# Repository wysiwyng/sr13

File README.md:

sr13 - MAI
====

the team MAI student robotics 2013 award winning code - see here: 
- http://www.youtube.com/watch?v=O69H89OFcbA
- https://www.studentrobotics.org/
- https://www.studentrobotics.org/news/2013-04-14_jaws_meet_floors

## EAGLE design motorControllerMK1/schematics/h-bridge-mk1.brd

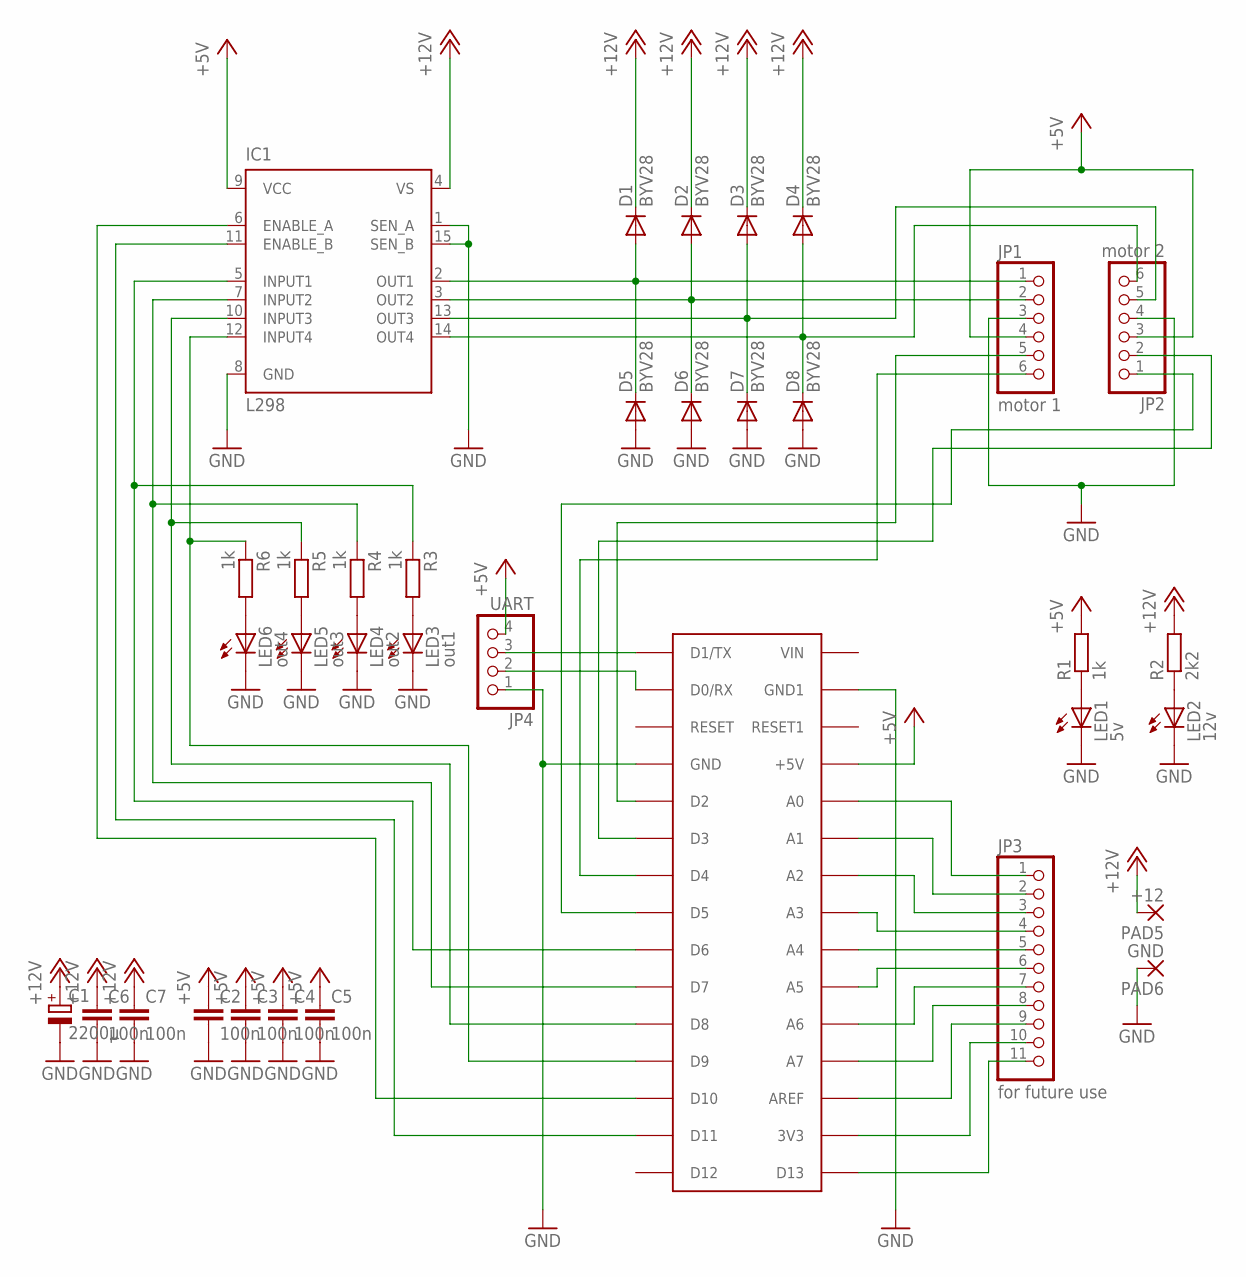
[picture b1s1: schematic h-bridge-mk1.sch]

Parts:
C1: 2200µ; E5-10,5
C2, C3, C4, C5, C6, C7: 100n; C025-025X050
D1, D2, D3, D4, D5, D6, D7, D8: BYV28; SOD64-10
IC1: L298; MULTIWATT-15
JP1: motor 1; 1X06
JP2: motor 2; 1X06
JP3: for future use; 1X11
JP4: UART; 1X04
LED1: 5v; LED3MM
LED2: 12v; LED3MM
LED3: out1; LED3MM
LED4: out2; LED3MM
LED5: out3; LED3MM
LED6: out4; LED3MM
PAD5: +12; 3,81/1,1
PAD6: GND; 3,81/1,1
R1, R3, R4, R5, R6: 1k; 0207/10
R2: 2k2; 0207/10
U$1: ARDUINONANO; PDIP-32

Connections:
+5V: C2.1, C3.1, C4.1, C5.1, IC1.9 (VCC), JP1.4, JP2.3, JP4.4, R1.2, U$1.+5V
+12V: C1.+, C6.1, C7.1, D1.C, D2.C, D3.C, D4.C, IC1.4 (VS), PAD5.1, R2.2
ENA: IC1.6 (ENABLE_A), U$1.D10
ENB: IC1.11 (ENABLE_B), U$1.D11
GND: C1.-, C2.2, C3.2, C4.2, C5.2, C6.2, C7.2, D5.A, D6.A, D7.A, D8.A, IC1.1 (SEN_A), IC1.8 (GND), IC1.15 (SEN_B), JP1.3, JP2.4, JP4.1, LED1.K (C), LED2.K (C), LED3.K (C), LED4.K (C), LED5.K (C), LED6.K (C), PAD6.1, U$1.GND, U$1.GND1
INA1: IC1.5 (INPUT1), R3.1, U$1.D6
INA2: IC1.7 (INPUT2), R4.1, U$1.D7
INB1: IC1.10 (INPUT3), R5.1, U$1.D8
INB2: IC1.12 (INPUT4), R6.1, U$1.D9
unnamed: JP3.1, U$1.A0
unnamed: JP3.2, U$1.A1
unnamed: JP3.3, U$1.A2
unnamed: JP3.4, U$1.A3
unnamed: JP2.2, U$1.D3
unnamed: JP1.6, U$1.D4
unnamed: JP2.1, U$1.D5
unnamed: JP3.5, U$1.A4
unnamed: JP1.5, U$1.D2
unnamed: JP3.6, U$1.A5
unnamed: JP3.7, U$1.A6
unnamed: JP3.8, U$1.A7
unnamed: JP3.9, U$1.AREF
unnamed: JP3.10, U$1.3V3
unnamed: JP3.11, U$1.D13
unnamed: LED1.A, R1.1
unnamed: LED2.A, R2.1
unnamed: LED3.A, R3.2
unnamed: LED4.A, R4.2
unnamed: LED5.A, R5.2
unnamed: LED6.A, R6.2
unnamed: JP4.3, U$1.D1/TX
unnamed: JP4.2, U$1.D0/RX
OUT1: D1.A, D5.C, IC1.2 (OUT1), JP1.1
OUT2: D2.A, D6.C, IC1.3 (OUT2), JP1.2
OUT3: D3.A, D7.C, IC1.13 (OUT3), JP2.5
OUT4: D4.A, D8.C, IC1.14 (OUT4), JP2.6

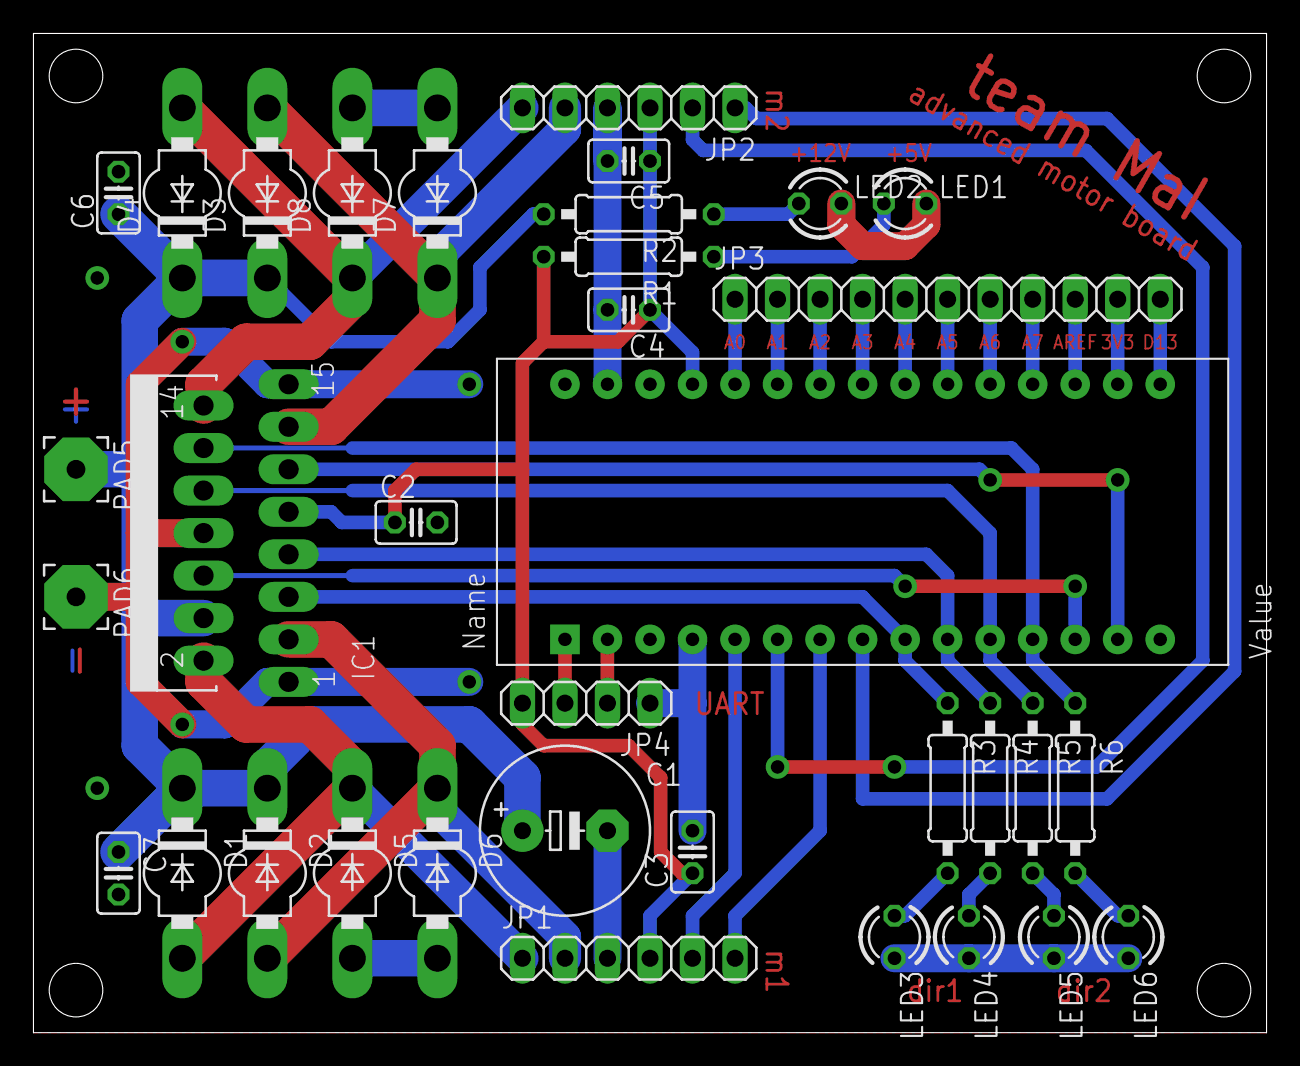
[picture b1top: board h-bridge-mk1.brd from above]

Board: 2 copper layers, 73.7 x 59.7 mm, 35 parts (0 on the bottom side), 36 nets.

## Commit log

2013-09-05 added lift controller code
